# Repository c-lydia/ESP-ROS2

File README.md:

# ESP-ROS2

micro-ROS workspace for ESP32 (FreeRTOS + ESP-IDF) with ROS 2 Humble, including both the Wall-E control stack and the Gassify gas-robot stack.

For a user-focused setup and operation guide, see [user_manual.md](user_manual.md).

This repository includes:

- ESP32 firmware app: `firmware/custom/esp32_controller`
- micro-ROS firmware workspace: `firmware/mcu_ws`
- Host ROS 2 workspace: `src`, `build`, `install`
- micro-ROS agent container (UDP 9999)
- Gas robot ROS 2 workspace: `gas_robot_ws/src`
- Gassify system model: `gassify_model.md`

## Documentation Map

- User guide: [user_manual.md](user_manual.md)
- Concepts guide: [concepts.md](concepts.md)
- Theoretical calculation summary: [notes.md](notes.md)
- Gassify mathematical model: [gassify_model.md](gassify_model.md)
- PCB and KiCad sources: [pcb/wall_e_pcb_v1.0](pcb/wall_e_pcb_v1.0)
- Sphinx docs index: `docs/source/index.rst`

## Gassify Stack Overview

The Gassify part of this repository focuses on gas-robot modeling and robot description assets alongside the existing Wall-E stack.

- ROS 2 package set location: `gas_robot_ws/src`
- Robot description package: `gas_robot_ws/src/gas_robot_description`
- URDF/Xacro model includes a dedicated gas sensor link (`gas_sensor_link`) in:
  - `gas_robot_ws/src/gas_robot_description/gas_robot_description/src/description/gas_robot.urdf.xacro`
- Full mathematical and control model reference: `gassify_model.md`

The Sphinx site includes the same high-level concepts and firmware details in a published format.

## Prerequisites

- Docker
- Docker Compose
- USB access for flashing (device usually `/dev/ttyUSB0`)

Optional for CUDA/GPU workflows:

- NVIDIA GPU driver on host
- NVIDIA Container Toolkit on host (`nvidia-container-toolkit`)

## Quick Start

From the repository root:

1. Start workspace and agent

``` bash
docker compose up -d
```

GPU/CUDA-enabled start (keeps default pipeline unchanged when not used):

``` bash
docker compose -f docker-compose.yaml -f docker-compose.gpu.yaml up --build -d
```

GPU image includes an object-detection-ready Python stack in this mode:

- CUDA-enabled PyTorch (`torch`, `torchvision`, `torchaudio`)
- `ultralytics` (YOLO)
- `opencv-python-headless`
- `onnx` and `onnxruntime-gpu==1.18.1` (pinned)
- `pycocotools`
- `tensorrt==8.6.1` (pinned)

To override TensorRT version, change `TENSORRT_PIP_SPEC` in `docker/docker-compose.gpu.yaml`.
To override ONNX Runtime GPU version, change `ONNXRUNTIME_GPU_PIP_SPEC` in `docker/docker-compose.gpu.yaml`.

Quick GPU check inside container:

``` bash
docker exec -it micro_ros_workspace bash -lc "nvidia-smi"
```

Quick Python GPU/object-detection check:

``` bash
docker exec -it micro_ros_workspace bash -lc "python3 -c 'import torch, ultralytics, cv2; print(torch.__version__); print(torch.cuda.is_available()); print(ultralytics.__version__); print(cv2.__version__)'"
```

Quick TensorRT check:

``` bash
docker exec -it micro_ros_workspace bash -lc "python3 -c 'import tensorrt as trt; print(trt.__version__)'"
```

2. Enter workspace container

``` bash
docker exec -it micro_ros_workspace bash
```

3. Build host ROS 2 workspace (if needed)

``` bash
cd /micro_ros_ws
colcon build
```

4. Source the environment

``` bash
source /opt/ros/humble/setup.bash
source /micro_ros_ws/install/setup.bash
```

If you launch RViz or Gazebo GUI from the container and see `Authorization required, but no authorization protocol specified`, run `xhost +si:localuser:root` on the host before starting the container. This workspace uses X11 forwarding, and the container runs as root by default.

## Launch and Visualization Updates (2026-04-17)

- `wall_e.launch.py` now generates `robot_description` using the Python xacro API (`xacro.process_file(...).toxml()`) instead of shelling out to the `xacro` executable.
- `gazebo_ros` remains optional at launch time. If unavailable, launch continues with a clear log message.
- Rear wheel TF visibility in RViz is now guaranteed even when `joint_state_publisher` is disabled:
  - rear wheel static TF publishers are started by default
  - they are automatically disabled when `use_joint_state_publisher:=true`
- Fresh containers should include runtime ROS GUI/model dependencies from `Dockerfile` (`ros-humble-xacro`, `ros-humble-rviz2`, `ros-humble-gazebo-ros-pkgs`, `ros-humble-joint-state-publisher`).

If your currently running container was created before these package updates, rebuild it:

``` bash
docker compose up --build -d
```

## KiCad In Docker

KiCad is available in the `workspace` container and the PCB project is mounted at:

``` bash
/micro_ros_ws/pcb/wall_e_pcb_v1.0
```

1. Verify KiCad CLI:

``` bash
docker exec micro_ros_workspace kicad-cli version
```

2. Run DRC report:

``` bash
docker exec micro_ros_workspace kicad-cli pcb drc /micro_ros_ws/pcb/wall_e_pcb_v1.0/wall_e.kicad_pcb
```

3. Export Gerbers:

``` bash
docker exec micro_ros_workspace kicad-cli pcb export gerbers /micro_ros_ws/pcb/wall_e_pcb_v1.0/wall_e.kicad_pcb --output /micro_ros_ws/pcb/wall_e_pcb_v1.0/gerbers
```

4. Launch KiCad GUI from container (host X11):

``` bash
xhost +si:localuser:root
docker exec -it micro_ros_workspace kicad
```

## Build ESP32 Firmware

Inside the workspace container:

1. Configure firmware app and transport

``` bash
ros2 run micro_ros_setup configure_firmware.sh esp32_controller -t udp -i 192.168.1.2 -p 8888
```

2. Build firmware

``` bash
ros2 run micro_ros_setup build_firmware.sh
```

3. Firmware output files

``` bash
firmware/freertos_apps/microros_esp32_extensions/build/esp32_controller.bin
firmware/freertos_apps/microros_esp32_extensions/build/esp32_controller.elf
```

## Flash ESP32 Firmware

Inside the workspace container (requires serial device access):

1. Flash

``` bash
ros2 run micro_ros_setup flash_firmware.sh
```

If your board is not `/dev/ttyUSB0`, update `docker-compose.yaml` device mapping or run a custom docker command with the correct `--device` mapping.

## Monitor ESP32 Logs (ESP-IDF)

Inside the workspace container:

``` bash
cd /micro_ros_ws/firmware/freertos_apps/microros_esp32_extensions
source /micro_ros_ws/firmware/toolchain/esp-idf/export.sh
idf.py -p /dev/ttyUSB0 monitor
```

You can also build then monitor:

``` bash
idf.py build
idf.py -p /dev/ttyUSB0 monitor
```

## Run In Wokwi (Simulation)

Wokwi does not use `/dev/ttyUSB0`. It loads your firmware `.bin`/`.elf` directly.

1. Ensure `wokwi.toml` points to the generated firmware files:

``` toml
[wokwi]
version = 1
firmware = "firmware/freertos_apps/microros_esp32_extensions/build/esp32_controller.bin"
elf = "firmware/freertos_apps/microros_esp32_extensions/build/esp32_controller.elf"
```

2. Build firmware before starting simulator:

``` bash
docker exec micro_ros_workspace bash -lc "cd /micro_ros_ws/firmware/freertos_apps/microros_esp32_extensions && source /micro_ros_ws/firmware/toolchain/esp-idf/export.sh && idf.py build"
```

3. Start Wokwi from VS Code command palette: `Wokwi: Start Simulator`.

4. Read logs in VS Code `Output` panel, `Wokwi` channel (or `Wokwi Terminal`, depending on extension version).

If logs still do not appear, stop simulation, reload VS Code window, and start simulator again.

## WiFi Provisioning System

Both ESP32 controller apps (motor-enabled and sensor-only) include a **browser-based WiFi provisioning system** for easy credential setup without source code editing.

### How It Works

1. **First Boot (No Credentials)**
   - Device starts WiFi access point: `ESP32-Setup` (open, no password)
   - HTTP provisioning server launches on `http://192.168.4.1/`

2. **User Setup**
   - Connect laptop/phone to `ESP32-Setup` network
   - Open browser to `http://192.168.4.1/`
   - Enter WiFi SSID and password via form
   - Device saves credentials to NVS flash (persistent)

3. **Subsequent Boots**
   - Device reads stored credentials from NVS
   - Connects to configured WiFi in normal station mode
   - Proceeds with ROS 2 and sensor initialization

### Credential Storage

- **Location**: NVS flash partition, namespace `"wifi_creds"`
- **Persistence**: Survives power cycles and resets
- **Fallback**: Kconfig symbols `CONFIG_ESP_WIFI_SSID` / `CONFIG_ESP_WIFI_PASSWORD` (for build-time defaults)

### Architecture

The provisioning system includes:

- `nvs_read_wifi_creds()`: Load SSID/password from flash
- `nvs_write_wifi_creds()`: Save credentials after form submission
- SoftAP initialization for open access point
- Simple HTML form with POST handler for credential entry
- Automatic server shutdown after successful provisioning

### Applicable Apps

- `firmware/custom/esp32_controller/`: Motor + sensor controller with full provisioning
- `firmware/freertos_apps/apps/esp32_controller/`: Sensor-only reference variant (provisioning included)

## Run micro-ROS Agent

The compose service starts this automatically:

``` bash
microros/micro-ros-agent:humble udp4 --port 9999
```

You can check logs with:

``` bash
docker logs -f micro_ros_agent
```

## Sensor Processing Pipeline (Host)

The firmware publishes raw sensor topics:

- `/imu/data` (`sensor_msgs/msg/Imu`)
- `/range/data` (`sensor_msgs/msg/Range`)

Host-side ROS 2 nodes can process these into cleaner and fused signals:

- `wall_e_ws/src/feedback/feedback/imu_filter.py`
  - Input: `/imu/data`
  - Output: `/imu/filter`
- `wall_e_ws/src/feedback/feedback/ultrasonic_filter.py`
  - Input: `/range/data`
  - Output: `/range/filter`
- `wall_e_ws/src/feedback/feedback/sensor_fusion.py`
  - Inputs: `/imu/filter`, `/range/filter`
  - Outputs: `/fusion/height`, `/fusion/vertical_velocity`, `/fusion/debug`

## PCB and Speed Sensing

The board design lives in [pcb/wall_e_pcb_v1.0](pcb/wall_e_pcb_v1.0).

The current schematic includes the ESP32 module, motor driver stages, the MPU6050, the HC-SR04 range sensor, and paired hall-effect sensors for wheel-speed or rotation feedback.

Use the KiCad project as the source of truth for connector pinouts, board placement, and DRC/GERBER work before changing firmware wiring assumptions.

This keeps firmware responsibilities focused on sensor I/O and control while allowing filter tuning on the host.

## Control and Localization Pipeline (Host)

Current host-side runtime flow:

- `control/gamepad_node`
  - Publishes `/gamepad`
- `control/robot_control_node`
  - Inputs: `/gamepad`, `/range/filter`, `/imu/filter`, `/odom`
  - Outputs: `/cmd_vel`, `/servo_cmd`
  - Supports manual mode and cascaded closed-loop mode:
    - outer P/PD position-to-speed setpoint
    - inner PI speed tracking loop
  - Also maps a gamepad axis to `/servo_cmd` (`std_msgs/msg/Float32`, angle in degrees)
- `localization/odometry_node`
  - Inputs: `/cmd_vel`, `/imu/filter`, `/range/filter`, `/fusion/height`, `/fusion/vertical_velocity`
  - Output: `/odom`
- `localization/inverse_kinematic_node`
  - Input: `/cmd_vel`
  - Output: `/motor_cmd` (4-wheel command array)

## System Architecture Diagram

Flow summary:

- `esp32_controller` publishes raw IMU and range data to ROS 2.
- `imu_filter` and `ultrasonic_filter` produce cleaner feedback streams.
- `sensor_fusion` combines filtered streams for downstream state estimation.
- `odometry_node` estimates vehicle state and publishes `/odom`.
- `robot_control_node` generates `/cmd_vel` using gamepad + safety + PI hold.
- `robot_control_node` also publishes `/servo_cmd` from gamepad axis input (with configurable limits/default).
- In closed-loop mode, PI acts on speed error (not direct position error).
- `inverse_kinematic_node` converts `/cmd_vel` into `/motor_cmd` for firmware actuation.

## Useful Commands

- Rebuild host workspace

``` bash
docker exec -it micro_ros_workspace bash -lc "cd /micro_ros_ws && colcon build"
```

- Rebuild firmware

``` bash
docker exec -it micro_ros_workspace bash -lc "source /opt/ros/humble/setup.bash && source /micro_ros_ws/install/setup.bash && ros2 run micro_ros_setup build_firmware.sh"
```

## Latest Firmware Debug Notes (2026-04-10)

- Confirmed firmware path in use is `firmware/custom/esp32_controller`.
- MPU startup now includes gyro bias calibration (`200` samples). Keep robot still at boot for best drift reduction.
- Ultrasonic timeout message `Ultrasonic timeout(wait high)` means no rising edge was seen on ECHO.
- After wiring/level correction, ultrasonic produced valid pulse widths around `344-401 us` (`~0.059-0.069 m` in test setup).
- Reboot right after `Starting ROS node setup...` was traced to watchdog interaction in startup; the firmware now logs watchdog delete/add status around ROS init.
- `NVS open for read failed: 0x1102` is expected when WiFi credentials are not yet stored in namespace `wifi_creds`.

- Stop everything

``` bash
docker compose down
```

## Troubleshooting

- Package `micro_ros_setup` not found
  Source both setup files:

``` bash
source /opt/ros/humble/setup.bash
source /micro_ros_ws/install/setup.bash
```

- Launch error: `file not found: [Errno 2] No such file or directory: 'xacro'`
  Install xacro in the running container (or rebuild image after pulling latest Dockerfile updates):

``` bash
apt-get update && apt-get install -y ros-humble-xacro
```

- Launch/CLI says `Package not found` for `rviz2` or `gazebo_ros`
  Your container is missing GUI/simulation runtime packages. Rebuild with the updated image:

``` bash
docker compose up --build -d
```

- RViz RobotModel shows `No transform from rear_left_wheel` or `rear_right_wheel`
  This is now handled in the launch file by publishing rear-wheel static transforms when `joint_state_publisher` is off.
  If you still see it, restart launch and verify you are using the updated `wall_e.launch.py`.

- Docker compose fails on `/dev/ttyUSB0`
  Your host may expose a different serial device. Adjust `docker-compose.yaml` accordingly.

- Build fails with Git safe.directory for esp-idf
  Run in container:

``` bash
git config --global --add safe.directory /micro_ros_ws/firmware/toolchain/esp-idf
```

- ESP-IDF monitor fails with `Device or resource busy: '/dev/ttyUSB0'`
  Another process is already using the serial port. Close any existing `screen`, `idf.py monitor`, or other serial tool and retry.
  To find the owner:

``` bash
fuser -v /dev/ttyUSB0
lsof /dev/ttyUSB0
```

- `make menuconfig` fails with `python: No such file or directory`
  Install Python alias in the container:

``` bash
apt-get update && apt-get install -y python-is-python3
```

- ESP-IDF Python dependency warnings (`pkg_resources`, setuptools)
  For ESP-IDF v4.1, pin setuptools in the IDF virtualenv:

``` bash
VENV=/root/.espressif/python_env/idf4.1_py3.10_env
$VENV/bin/python -m pip install --upgrade pip
$VENV/bin/python -m pip install "setuptools<81" wheel
```

- Runtime crash: `assertion "netif" failed` in `esp_netif_create_default_wifi_sta`
  Cause: duplicate default STA netif creation.
  Fix applied in:
  - `firmware/freertos_apps/apps/esp32_controller/app.c`
  - `firmware/custom/esp32_controller/app.c`

  If this reappears after syncing app sources, ensure Wi-Fi init runs once and `esp_netif_create_default_wifi_sta()` is not called multiple times.

- Wi-Fi behavior on mobile hotspots
  If connection is unstable, force hotspot to 2.4 GHz WPA2 and disable battery-saving/idle sleep on the phone.

- Wokwi simulator starts but no logs are visible
  Usually caused by stale build artifacts or viewing the wrong panel.
  Rebuild firmware, restart simulation, and check VS Code `Output` -> `Wokwi`.

## Project Layout

- `src`: ROS 2 packages
- `firmware/custom/esp32_controller: app source`
- `firmware/freertos_apps/microros_esp32_extensions`: generated ESP-IDF project
- `firmware/mcu_ws`: micro-ROS cross-compiled workspace
- `docs`: Sphinx documentation

## References (Books and Research Papers)

- Mahony, R., Hamel, T., and Pflimlin, J.-M. (2008). Nonlinear Complementary Filters on the Special Orthogonal Group. *IEEE Transactions on Automatic Control*, 53(5), 1203-1218.
- Madgwick, S. O. H. (2010). *An efficient orientation filter for inertial and inertial/magnetic sensor arrays*. University of Bristol, Technical Report.
- Thrun, S., Burgard, W., and Fox, D. (2005). *Probabilistic Robotics*. MIT Press.
- Siciliano, B., Sciavicco, L., Villani, L., and Oriolo, G. (2009). *Robotics: Modelling, Planning and Control*. Springer.
- Astrom, K. J., and Murray, R. M. (2008). *Feedback Systems: An Introduction for Scientists and Engineers*. Princeton University Press.

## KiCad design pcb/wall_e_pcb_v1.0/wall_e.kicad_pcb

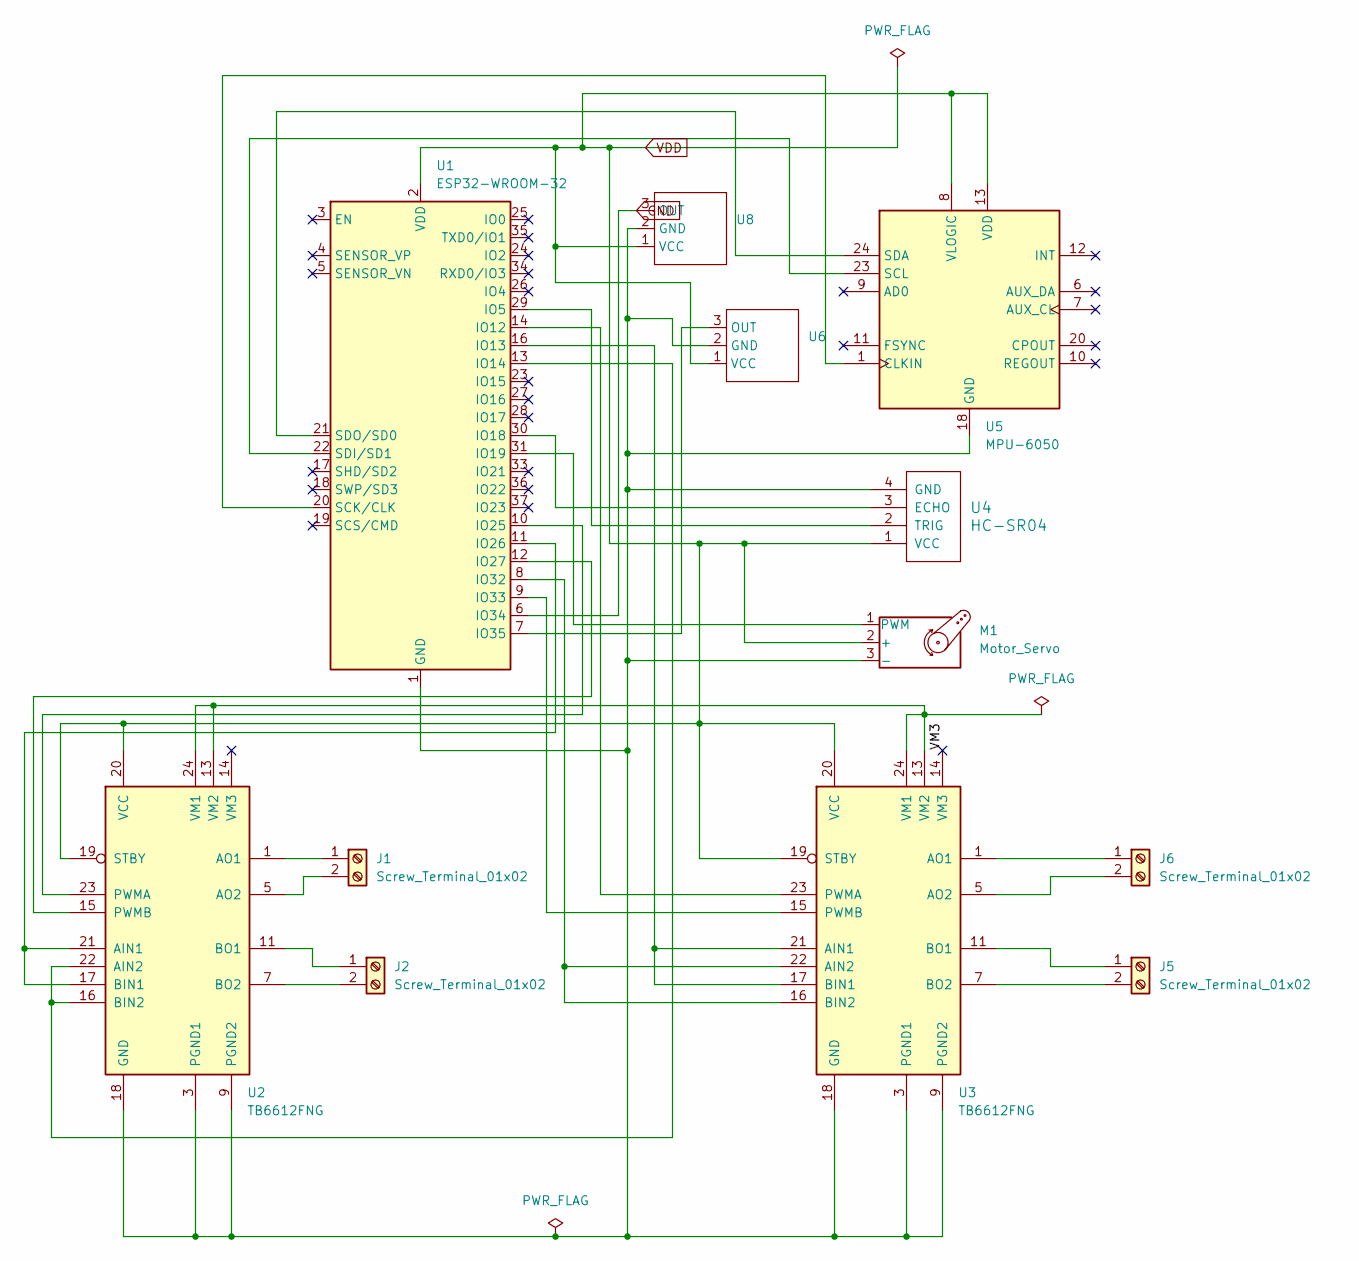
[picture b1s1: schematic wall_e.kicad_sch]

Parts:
J1, J2, J5, J6: Screw_Terminal_01x02; TerminalBlock_Phoenix_MKDS-1,5-2-5.08_1x02_P5.08mm_Horizont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
M1: Motor_Servo; PinHeader_1x03_P2.54mm_Vertical
U1: ESP32-WROOM-32
U2, U3: TB6612FNG; SSOP-24_5.3x8.2mm_P0.65mm
U4: HC-SR04; PinHeader_1x04_P2.54mm_Vertical
U5: MPU-6050; InvenSense_QFN-24_4x4mm_P0.5mm
U6, U8: PinHeader_1x03_P2.54mm_Vertical

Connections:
/VM3: U3.14 (VM3)
GND: U1.6 (IO34), U8.3 (OUT)
unnamed: J1.1, U2.1 (AO1), U2.2 (AO1)
unnamed: J1.2, U2.5 (AO2), U2.6 (AO2)
unnamed: J2.1, U2.11 (BO1), U2.12 (BO1)
unnamed: J2.2, U2.7 (BO2), U2.8 (BO2)
unnamed: J5.1, U3.11 (BO1), U3.12 (BO1)
unnamed: J5.2, U3.7 (BO2), U3.8 (BO2)
unnamed: J6.1, U3.1 (AO1), U3.2 (AO1)
unnamed: J6.2, U3.5 (AO2), U3.6 (AO2)
unnamed: M1.3 (-), U1.1 (GND), U1.15 (GND), U1.38 (GND), U1.39 (GND), U2.3 (PGND1), U2.4 (PGND1), U2.9 (PGND2), U2.10 (PGND2), U2.18 (GND), U3.3 (PGND1), U3.4 (PGND1), U3.9 (PGND2), U3.10 (PGND2), U3.18 (GND), U4.4 (GND), U5.18 (GND), U6.2 (GND), U8.2 (GND)
unnamed: M1.1 (PWM), U1.31 (IO19)
unnamed: U1.29 (IO5), U4.2 (TRIG)
unnamed: U1.14 (IO12), U3.23 (PWMA)
unnamed: U1.16 (IO13), U3.17 (BIN1), U3.21 (AIN1)
unnamed: U1.13 (IO14), U2.16 (BIN2), U2.22 (AIN2)
unnamed: U1.30 (IO18), U4.3 (ECHO)
unnamed: U1.10 (IO25), U2.23 (PWMA)
unnamed: U1.11 (IO26), U2.17 (BIN1), U2.21 (AIN1)
unnamed: U1.12 (IO27), U2.15 (PWMB)
unnamed: U1.8 (IO32), U3.16 (BIN2), U3.22 (AIN2)
unnamed: U1.9 (IO33), U3.15 (PWMB)
unnamed: U1.7 (IO35), U6.3 (OUT)
unnamed: U1.20 (SCK/CLK), U5.1 (CLKIN)
unnamed: U1.22 (SDI/SD1), U5.23 (SCL)
unnamed: U1.21 (SDO/SD0), U5.24 (SDA)
unnamed: U2.13 (VM2), U2.24 (VM1), U3.13 (VM2), U3.24 (VM1)
VDD: M1.2 (+), U1.2 (VDD), U2.19 (STBY), U2.20 (VCC), U3.19 (STBY), U3.20 (VCC), U4.1 (VCC), U5.8 (VLOGIC), U5.13 (VDD), U6.1 (VCC), U8.1 (VCC)

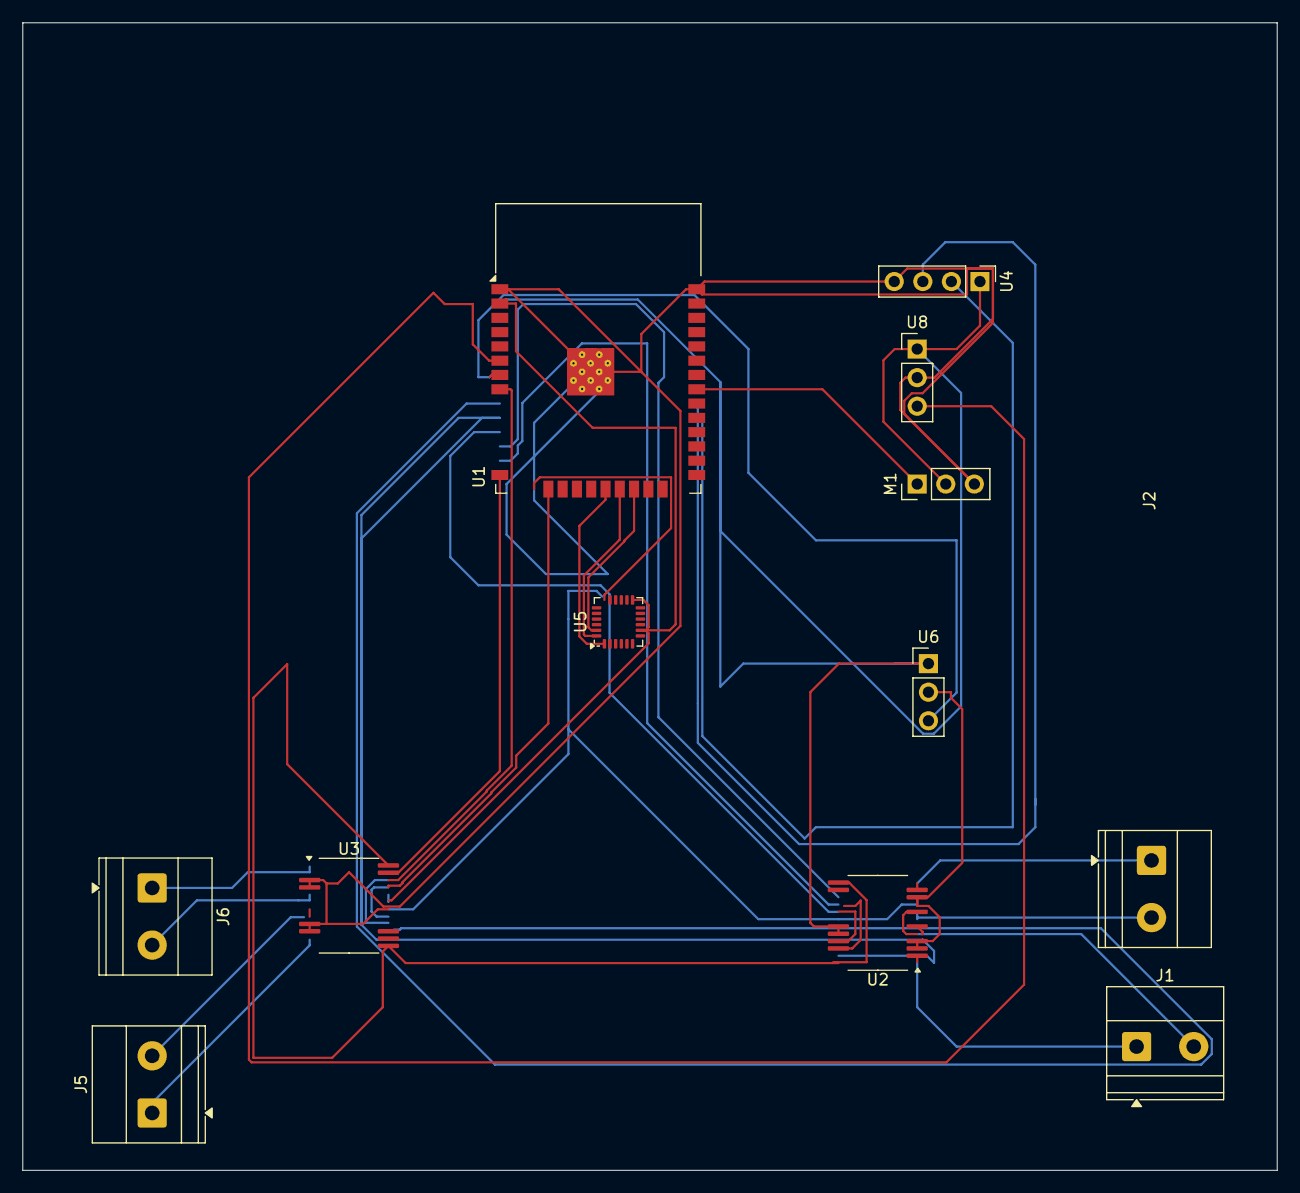
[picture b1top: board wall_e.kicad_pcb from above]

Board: 2 copper layers, 111.5 x 102.0 mm, 12 parts (0 on the bottom side), 27 nets.

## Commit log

2026-04-03 Add ESP32 controller firmware documentation and docs/source structure
2026-04-03 Add custom ESP32 controller firmware code and update WiFi documentation
2026-04-03 Enhance PDF documentation appearance and content structure
    - Dramatically improve documentation layout and visual hierarchy
    - Rewrite index.rst with professional structure and comprehensive overview
    - Add detailed section descriptions for capabilities and features
    - Include technical stack table with all system components
    - Improve typography with better spacing and formatting
    - Create more compelling project introduction
2026-04-03 Add comprehensive code snippets and improve syntax highlighting
    Enhance ESP32 controller documentation with:
    - Real C code examples for all major functions
    - Syntax-highlighted code blocks with proper formatting
    - app_main() initialization sequence
    - timer_callback() sensor publishing loop
    - WiFi initialization implementation
2026-04-03 Transform code snippets to light gray theme with rounded corners
    Complete redesign of code block styling for a cleaner, more modern look:
    PDF & HTML Styling:
    - Change code block background from dark (#272822) to light gray (#f5f5f5)
    - Add rounded corners (8px border-radius) for modern appearance
    - Replace sharp box edges with smooth rounded design
    - Light gray borders (#ccc) for subtle definition
2026-04-03 Fix CSS styling with important flags to override RTD theme
2026-04-03 Update documentation styling: light gray rounded code blocks with professional syntax highlighting and Sphinx configuration refinements
2026-04-04 docs: Update syntax highlighting in HTML build
2026-04-04 restore: Restore full RTD theme options for better documentation display
2026-04-04 fix: Rebuild with clean RTD theme configuration
2026-04-04 style: Simplify and aggressively override syntax highlighting colors
2026-04-04 revert: Remove custom CSS overrides and return to standard RTD theme
2026-04-04 chore: Rebuild documentation with clean RTD theme
2026-04-04 add: Add .nojekyll to enable proper GitHub Pages asset serving
2026-04-06 resolve path conflict, update README
2026-04-06 docs: trigger a fresh pages build
2026-04-06 ci: update pages actions
2026-04-08 add control stack
2026-04-10 fix sensor bugs
2026-04-16 Check for DOCKER secret in workflow
    Add a step to check for the presence of the DOCKER secret before proceeding.
2026-04-17 Update Docker image tags in workflow file
2026-04-20 add hall effect speed sensor
2026-04-20 Remove pip cache from Python setup in workflow
    Removed pip caching from Python setup step.
2026-04-20 Add GitHub Actions workflow for Jekyll deployment
    This workflow automates the building and deployment of a Jekyll site to GitHub Pages, including steps for checking out the code, building the site, and deploying it.
2026-04-20 fix deployment
2026-04-20 update docs
2026-04-20 Update issue templates
2026-04-20 Add GitHub Sponsors username for funding
2026-04-20 Add badges to README for project metrics
    Added badges for stars, forks, watchers, release, issues, and visitors.
2026-04-20 Add badges for various technologies in README
2026-04-21 add reference
2026-05-06 add gas detection robot packages
2026-05-06 add .gitignore
2026-05-07 add camera node
2026-05-07 update env config
2026-05-11 update stack

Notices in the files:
README.md:
License: Apache 2.0
